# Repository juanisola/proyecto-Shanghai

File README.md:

# proyecto-Shanghai

Integrantes:

Isola Juan Cruz 5 2 avionica comision b

Lin Rodrigo 5 2 avionica comision b

Somoza Juan Cruz 5 2 avionica comision b

Tolosa Santino5 2 avionica comision b

página: https://sites.google.com/impatrq.com/asdas/proyecto/proceso?authuser=1&pli=1

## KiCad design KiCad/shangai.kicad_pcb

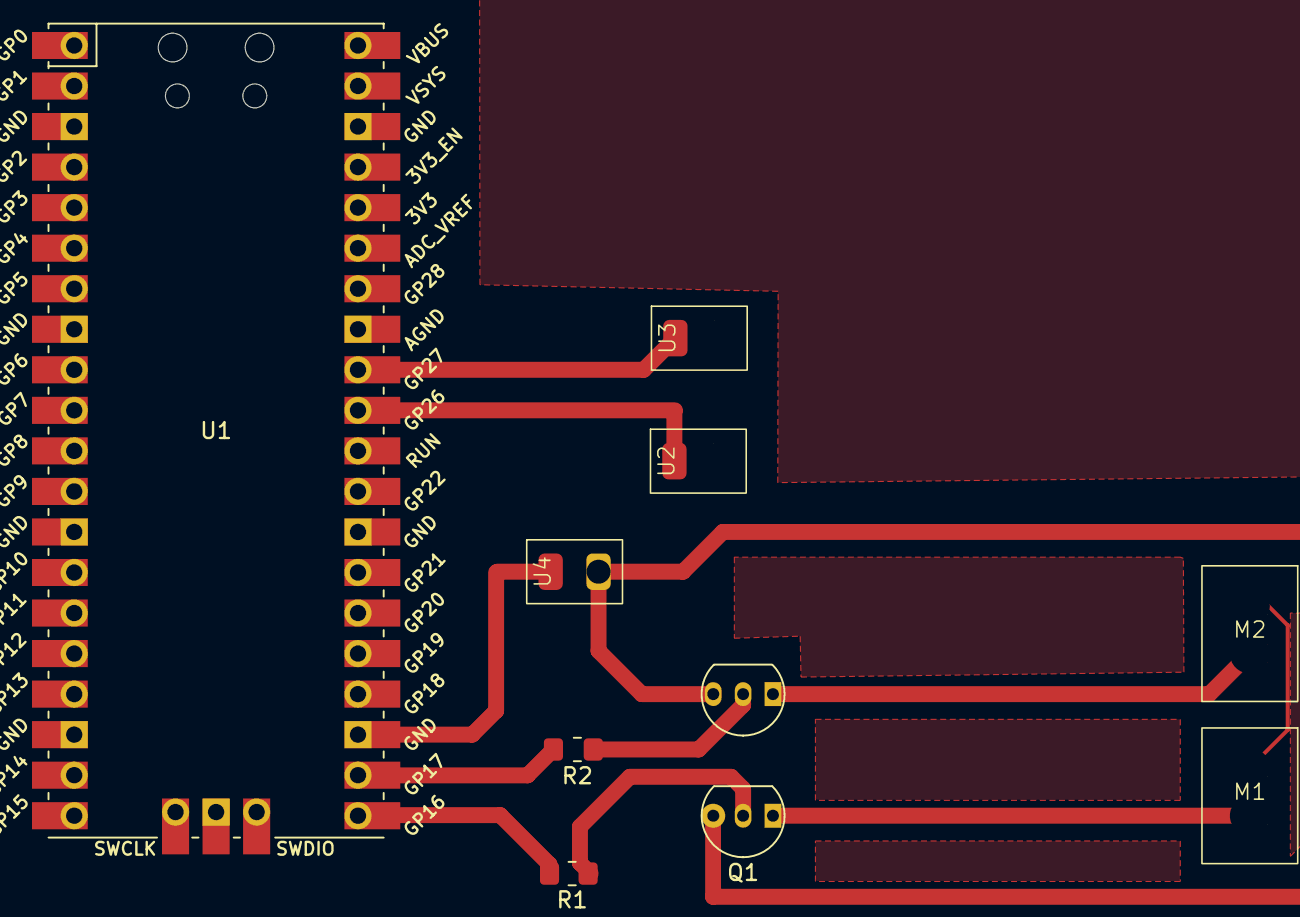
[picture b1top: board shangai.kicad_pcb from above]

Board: 2 copper layers, 10 parts (0 on the bottom side), 11 nets.

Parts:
M1, M2: Motor_AC; paso a paso
Q1, Q2: BC337; TO-92_Inline
R1, R2: 1k; R_0805_2012Metric_Pad1.20x1.40mm_HandSolder
U1: Pico; RPi_Pico_SMD_TH
U2, U3, U4: punto para conectar

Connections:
+9V: M1.1, M2.1
unnamed: Q1.2 (B), R1.1
unnamed: M1.2, Q1.1 (C)
unnamed: Q1.3 (E), Q2.3 (E), U4.2 (out)
unnamed: Q2.2 (B), R2.1
unnamed: M2.2, Q2.1 (C)
unnamed: R1.2, U1.21 (GPIO16)
unnamed: R2.2, U1.22 (GPIO17)
unnamed: U1.31 (GPIO26_ADC0), U2.1 (in)
unnamed: U1.32 (GPIO27_ADC1), U3.1 (in)
unnamed: U1.23 (GND), U4.1 (in)

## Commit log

2023-11-29 Create hola
2023-11-29 Create non
2023-11-29 Create wi
2023-11-29 Create chau
2023-11-29 Create v
2023-11-29 Create b
2023-11-29 Create f
2023-11-29 Create li
2023-12-03 Create d
